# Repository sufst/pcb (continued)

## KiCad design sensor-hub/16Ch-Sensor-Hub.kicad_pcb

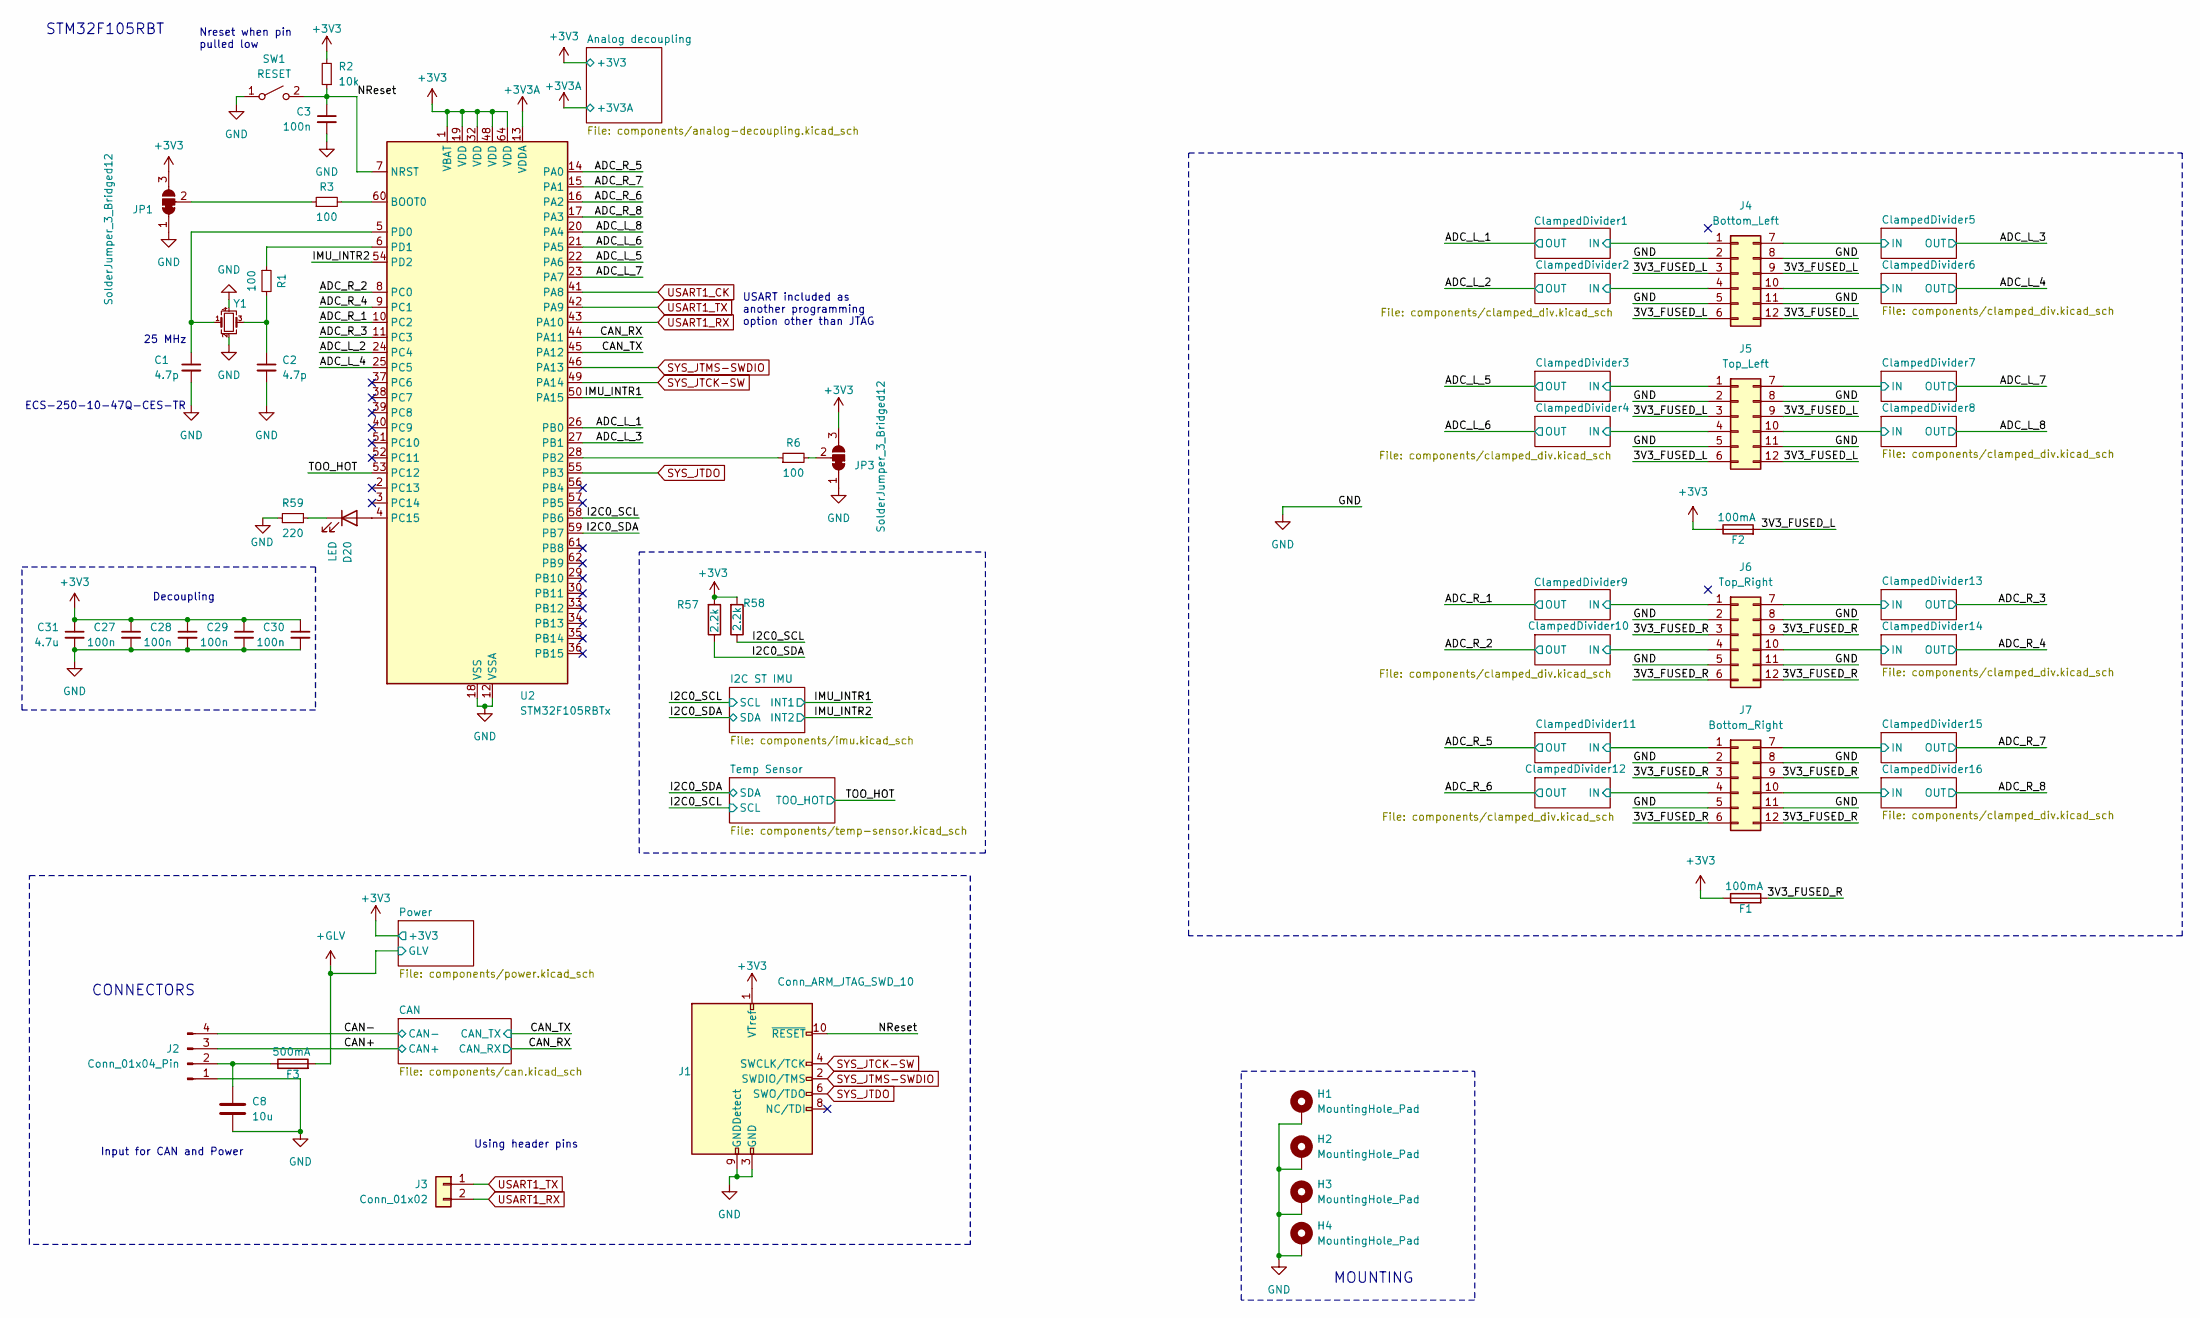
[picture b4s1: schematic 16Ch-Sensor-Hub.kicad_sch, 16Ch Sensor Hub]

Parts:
C1, C2: 4.7p; C_0603_1608Metric_Pad1.08x0.95mm_HandSolder
C3, C27, C28, C29, C30: 100n; C_0603_1608Metric_Pad1.08x0.95mm_HandSolder
C8: 10u; C_0603_1608Metric_Pad1.08x0.95mm_HandSolder
C31: 4.7u; C_0603_1608Metric_Pad1.08x0.95mm_HandSolder
D20: LED; LED_0603_1608Metric_Pad1.05x0.95mm_HandSolder
F1, F2: 100mA; Fuse_0603_1608Metric_Pad1.05x0.95mm_HandSolder
F3: 500mA; Fuse_0603_1608Metric_Pad1.05x0.95mm_HandSolder
H1, H2, H3, H4: MountingHole_Pad; MountingHole_3.2mm_M3_Pad_Via
J1: Conn_ARM_JTAG_SWD_10; SHF10501LDSMLC; MPN SHF-105-01-L-D-SM-LC
J2: Conn_01x04_Pin; Molex_Micro-Fit_3.0_43045-0412_2x02_P3.00mm_Vertical
J3: Conn_01x02; PinHeader_1x02_P2.54mm_Vertical
J4: Bottom_Left; Molex_Micro-Fit_3.0_43045-1200_2x06_P3.00mm_Horizontal
J5: Top_Left; Molex_Micro-Fit_3.0_43045-1200_2x06_P3.00mm_Horizontal
J6: Top_Right; Molex_Micro-Fit_3.0_43045-1200_2x06_P3.00mm_Horizontal
J7: Bottom_Right; Molex_Micro-Fit_3.0_43045-1200_2x06_P3.00mm_Horizontal
JP1, JP3: SolderJumper_3_Bridged12; SolderJumper-3_P1.3mm_Bridged12_RoundedPad1.0x1.5mm
R1, R3, R6: 100; R_0603_1608Metric_Pad0.98x0.95mm_HandSolder
R2: 10k; R_0603_1608Metric_Pad0.98x0.95mm_HandSolder
R57, R58: 2.2k; R_0603_1608Metric_Pad0.98x0.95mm_HandSolder; Mouser Order Number 603-RC0402FR-072K2L
R59: 220; R_0603_1608Metric_Pad0.98x0.95mm_HandSolder
SW1: RESET; SW_Push_1P1T_NO_CK_KMR2; MPN KMR221NG LFS
U2: STM32F105RBTx; LQFP-64_10x10mm_P0.5mm
Y1: ECS-250-10-47Q-CES-TR; Resonator_SMD_ECS_ECX-1247Q_1.6x1.2x0.3mm; MPN ECS-250-10-47Q-CES-TR

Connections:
+3V3: C27.1, C28.1, C29.1, C30.1, C31.1, F1.1, F2.1, J1.1 (VTref), JP1.3 (B), JP3.3 (B), R2.2, R57.2, R58.2, U2.1 (VBAT), U2.19 (VDD), U2.32 (VDD), U2.48 (VDD), U2.64 (VDD); also elsewhere on the board
+3V3A: U2.13 (VDDA); also elsewhere on the board
+GLV: F3.2; also elsewhere on the board
/3V3_FUSED_L: F2.2, J4.3, J4.6, J4.9, J4.12, J5.3, J5.6, J5.9, J5.12
/3V3_FUSED_R: F1.2, J6.3, J6.6, J6.9, J6.12, J7.3, J7.6, J7.9, J7.12
/ADC_L_1: U2.26 (PB0); also elsewhere on the board
/ADC_L_2: U2.24 (PC4); also elsewhere on the board
/ADC_L_3: U2.27 (PB1); also elsewhere on the board
/ADC_L_4: U2.25 (PC5); also elsewhere on the board
/ADC_L_5: U2.22 (PA6); also elsewhere on the board
/ADC_L_6: U2.21 (PA5); also elsewhere on the board
/ADC_L_7: U2.23 (PA7); also elsewhere on the board
/ADC_L_8: U2.20 (PA4); also elsewhere on the board
/ADC_R_1: U2.10 (PC2); also elsewhere on the board
/ADC_R_2: U2.8 (PC0); also elsewhere on the board
/ADC_R_3: U2.11 (PC3); also elsewhere on the board
/ADC_R_4: U2.9 (PC1); also elsewhere on the board
/ADC_R_5: U2.14 (PA0); also elsewhere on the board
/ADC_R_6: U2.16 (PA2); also elsewhere on the board
/ADC_R_7: U2.15 (PA1); also elsewhere on the board
/ADC_R_8: U2.17 (PA3); also elsewhere on the board
/CAN+: J2.3; also elsewhere on the board
/CAN-: J2.4; also elsewhere on the board
/CAN_RX: U2.44 (PA11); also elsewhere on the board
/CAN_TX: U2.45 (PA12); also elsewhere on the board
/ClampedDivider1/IN: J4.1; also elsewhere on the board
/ClampedDivider2/IN: J4.4; also elsewhere on the board
/ClampedDivider3/IN: J5.1; also elsewhere on the board
/ClampedDivider4/IN: J5.4; also elsewhere on the board
/ClampedDivider5/IN: J4.7; also elsewhere on the board
/ClampedDivider6/IN: J4.10; also elsewhere on the board
/ClampedDivider7/IN: J5.7; also elsewhere on the board
/ClampedDivider8/IN: J5.10; also elsewhere on the board
/ClampedDivider9/IN: J6.1; also elsewhere on the board
/ClampedDivider10/IN: J6.4; also elsewhere on the board
/ClampedDivider11/IN: J7.1; also elsewhere on the board
/ClampedDivider12/IN: J7.4; also elsewhere on the board
/ClampedDivider13/IN: J6.7; also elsewhere on the board
/ClampedDivider14/IN: J6.10; also elsewhere on the board
/ClampedDivider15/IN: J7.7; also elsewhere on the board
/ClampedDivider16/IN: J7.10; also elsewhere on the board
/I2C0_SCL: R58.1, U2.58 (PB6); also elsewhere on the board
/I2C0_SDA: R57.1, U2.59 (PB7); also elsewhere on the board
/IMU_INTR1: U2.50 (PA15); also elsewhere on the board
/IMU_INTR2: U2.54 (PD2); also elsewhere on the board
/NReset: C3.1, J1.10 (~RESET), R2.1, SW1.2 (B), U2.7 (NRST)
/TOO_HOT: U2.53 (PC12); also elsewhere on the board
GND: C1.2, C2.2, C3.2, C8.2, C27.2, C28.2, C29.2, C30.2, C31.2, H1.1, H2.1, H3.1, H4.1, J1.3 (GND), J1.5 (GND), J1.9 (GNDDetect), J2.1, J4.2, J4.5, J4.8, J4.11, J5.2, J5.5, J5.8, J5.11, J6.2, J6.5, J6.8, J6.11, J7.2, J7.5, J7.8, J7.11, JP1.1 (A), JP3.1 (A), R59.1, SW1.1 (A), U2.12 (VSSA), U2.18 (VSS), U2.31 (VSS), U2.47 (VSS), U2.63 (VSS), Y1.2, Y1.4; also elsewhere on the board
unnamed: C2.1, R1.2, Y1.3
unnamed: D20.2 (A), U2.4 (PC15)
unnamed: D20.1 (K), R59.2
unnamed: C8.1, F3.1, J2.2
unnamed: JP1.2 (C), R3.1
unnamed: JP3.2 (C), R6.2
unnamed: R3.2, U2.60 (BOOT0)
unnamed: R6.1, U2.28 (PB2)
unnamed: C1.1, U2.5 (PD0), Y1.1
unnamed: R1.1, U2.6 (PD1)
SYS_JTCK-SW: J1.4 (SWCLK/TCK), U2.49 (PA14)
SYS_JTDO: J1.6 (SWO/TDO), U2.55 (PB3)
SYS_JTMS-SWDIO: J1.2 (SWDIO/TMS), U2.46 (PA13)
USART1_CK: U2.41 (PA8)
USART1_RX: J3.2, U2.43 (PA10)
USART1_TX: J3.1, U2.42 (PA9)

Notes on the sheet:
25 MHz
STM32F105RBT
Input for CAN and Power
CONNECTORS
Nreset when pin pulled low
ECS-250-10-47Q-CES-TR
Decoupling
Using header pins
USART included as another programming option other than JTAG
MOUNTING

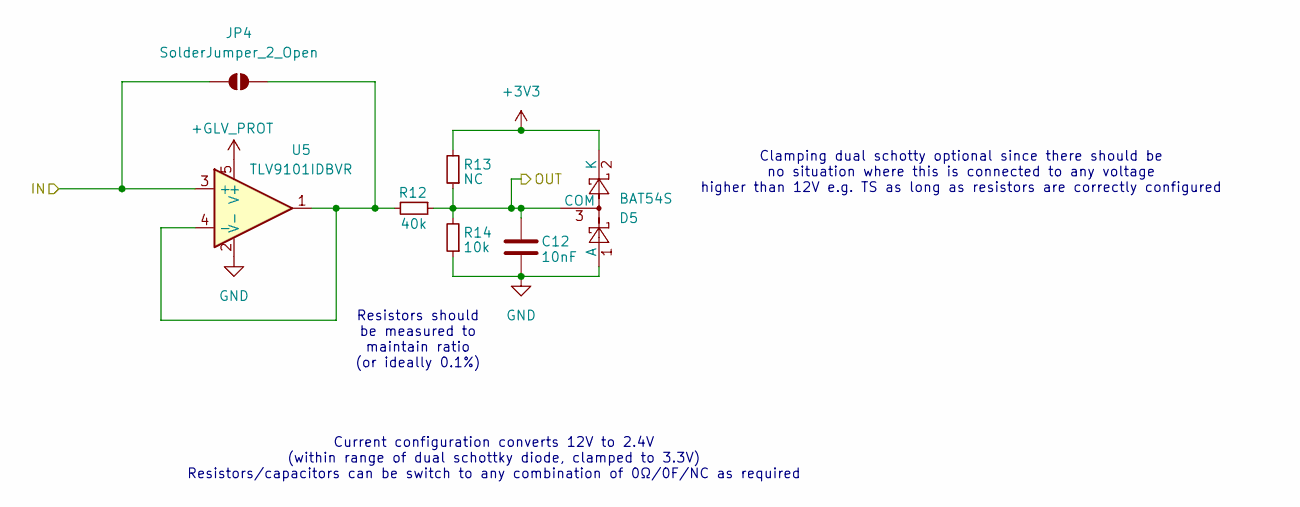
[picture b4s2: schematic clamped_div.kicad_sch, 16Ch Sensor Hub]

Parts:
C12: 10nF; C_0603_1608Metric_Pad1.08x0.95mm_HandSolder
D5: BAT54S; SOT-23
JP4: SolderJumper_2_Open; SolderJumper-2_P1.3mm_Open_RoundedPad1.0x1.5mm
R12: 40k; R_0603_1608Metric_Pad0.98x0.95mm_HandSolder; Manufacturer_Part_Number CRCW080540K0FKEA; Mouser Part Number 71-CRCW080540K0FKEA
R13: NC; R_0603_1608Metric_Pad0.98x0.95mm_HandSolder; Manufacturer_Part_Number CRGH0805F12R; Mouser Part Number 279-CRGH0805F12R
R14: 10k; R_0603_1608Metric_Pad0.98x0.95mm_HandSolder; Manufacturer_Part_Number CRGH0805F12R; Mouser Part Number 279-CRGH0805F12R
U5: TLV9101IDBVR; SOT-23-5_HandSoldering

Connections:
+3V3: D5.2 (K), R13.2; also elsewhere on the board
+GLV_PROT: U5.5 (V+); also elsewhere on the board
/ADC_L_4: C12.1, D5.3 (COM), R12.1, R13.1, R14.2; also elsewhere on the board
/ClampedDivider6/IN: JP4.1 (A), U5.3 (+); also elsewhere on the board
GND: C12.2, D5.1 (A), R14.1, U5.2 (V-); also elsewhere on the board
unnamed: JP4.2 (B), R12.2, U5.1, U5.4 (-)

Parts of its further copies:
C11, C13, C14, C15, C16, C17, C18, C19, C20, C21, C22, C23, C24, C25, C26: 10nF; C_0603_1608Metric_Pad1.08x0.95mm_HandSolder
D4, D6, D7, D8, D9, D10, D11, D12, D13, D14, D15, D16, D17, D18, D19: BAT54S; SOT-23
JP5, JP6, JP7, JP8, JP9, JP10, JP11, JP12, JP13, JP14, JP15, JP16, JP17, JP18, JP19: SolderJumper_2_Open; SolderJumper-2_P1.3mm_Open_RoundedPad1.0x1.5mm
R9, R15, R18, R21, R24, R27, R30, R33, R36, R39, R42, R45, R48, R51, R54: 40k; R_0603_1608Metric_Pad0.98x0.95mm_HandSolder; Manufacturer_Part_Number CRCW080540K0FKEA; Mouser Part Number 71-CRCW080540K0FKEA
R10, R16, R19, R22, R25, R28, R31, R34, R37, R40, R43, R46, R49, R52, R55: NC; R_0603_1608Metric_Pad0.98x0.95mm_HandSolder; Manufacturer_Part_Number CRGH0805F12R; Mouser Part Number 279-CRGH0805F12R
R11, R17, R20, R23, R26, R29, R32, R35, R38, R41, R44, R47, R50, R53, R56: 10k; R_0603_1608Metric_Pad0.98x0.95mm_HandSolder; Manufacturer_Part_Number CRGH0805F12R; Mouser Part Number 279-CRGH0805F12R
U4, U6, U7, U8, U9, U10, U11, U12, U13, U14, U15, U16, U17, U18, U19: TLV9101IDBVR; SOT-23-5_HandSoldering

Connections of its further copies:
+3V3: D4.2 (K), D6.2 (K), D7.2 (K), D8.2 (K), D9.2 (K), D10.2 (K), D11.2 (K), D12.2 (K), D13.2 (K), D14.2 (K), D15.2 (K), D16.2 (K), D17.2 (K), D18.2 (K), D19.2 (K), R10.2, R16.2, R19.2, R22.2, R25.2, R28.2, R31.2, R34.2, R37.2, R40.2, R43.2, R46.2, R49.2, R52.2, R55.2; also elsewhere on the board
+GLV_PROT: U4.5 (V+), U6.5 (V+), U7.5 (V+), U8.5 (V+), U9.5 (V+), U10.5 (V+), U11.5 (V+), U12.5 (V+), U13.5 (V+), U14.5 (V+), U15.5 (V+), U16.5 (V+), U17.5 (V+), U18.5 (V+), U19.5 (V+); also elsewhere on the board
/ADC_L_1: C15.1, D8.3 (COM), R21.1, R22.1, R23.2; also elsewhere on the board
/ADC_L_2: C16.1, D9.3 (COM), R24.1, R25.1, R26.2; also elsewhere on the board
/ADC_L_3: C11.1, D4.3 (COM), R9.1, R10.1, R11.2; also elsewhere on the board
/ADC_L_5: C17.1, D10.3 (COM), R27.1, R28.1, R29.2; also elsewhere on the board
/ADC_L_6: C18.1, D11.3 (COM), R30.1, R31.1, R32.2; also elsewhere on the board
/ADC_L_7: C13.1, D6.3 (COM), R15.1, R16.1, R17.2; also elsewhere on the board
/ADC_L_8: C14.1, D7.3 (COM), R18.1, R19.1, R20.2; also elsewhere on the board
/ADC_R_1: C23.1, D16.3 (COM), R45.1, R46.1, R47.2; also elsewhere on the board
/ADC_R_2: C24.1, D17.3 (COM), R48.1, R49.1, R50.2; also elsewhere on the board
/ADC_R_3: C19.1, D12.3 (COM), R33.1, R34.1, R35.2; also elsewhere on the board
/ADC_R_4: C20.1, D13.3 (COM), R36.1, R37.1, R38.2; also elsewhere on the board
/ADC_R_5: C25.1, D18.3 (COM), R51.1, R52.1, R53.2; also elsewhere on the board
/ADC_R_6: C26.1, D19.3 (COM), R54.1, R55.1, R56.2; also elsewhere on the board
/ADC_R_7: C21.1, D14.3 (COM), R39.1, R40.1, R41.2; also elsewhere on the board
/ADC_R_8: C22.1, D15.3 (COM), R42.1, R43.1, R44.2; also elsewhere on the board
/ClampedDivider1/IN: JP8.1 (A), U8.3 (+); also elsewhere on the board
/ClampedDivider2/IN: JP9.1 (A), U9.3 (+); also elsewhere on the board
/ClampedDivider3/IN: JP10.1 (A), U10.3 (+); also elsewhere on the board
/ClampedDivider4/IN: JP11.1 (A), U11.3 (+); also elsewhere on the board
/ClampedDivider5/IN: JP5.1 (A), U4.3 (+); also elsewhere on the board
/ClampedDivider7/IN: JP6.1 (A), U6.3 (+); also elsewhere on the board
/ClampedDivider8/IN: JP7.1 (A), U7.3 (+); also elsewhere on the board
/ClampedDivider9/IN: JP16.1 (A), U16.3 (+); also elsewhere on the board
/ClampedDivider10/IN: JP17.1 (A), U17.3 (+); also elsewhere on the board
/ClampedDivider11/IN: JP18.1 (A), U18.3 (+); also elsewhere on the board
/ClampedDivider12/IN: JP19.1 (A), U19.3 (+); also elsewhere on the board
/ClampedDivider13/IN: JP12.1 (A), U12.3 (+); also elsewhere on the board
/ClampedDivider14/IN: JP13.1 (A), U13.3 (+); also elsewhere on the board
/ClampedDivider15/IN: JP14.1 (A), U14.3 (+); also elsewhere on the board
/ClampedDivider16/IN: JP15.1 (A), U15.3 (+); also elsewhere on the board
GND: C11.2, C13.2, C14.2, C15.2, C16.2, C17.2, C18.2, C19.2, C20.2, C21.2, C22.2, C23.2, C24.2, C25.2, C26.2, D4.1 (A), D6.1 (A), D7.1 (A), D8.1 (A), D9.1 (A), D10.1 (A), D11.1 (A), D12.1 (A), D13.1 (A), D14.1 (A), D15.1 (A), D16.1 (A), D17.1 (A), D18.1 (A), D19.1 (A), R11.1, R17.1, R20.1, R23.1, R26.1, R29.1, R32.1, R35.1, R38.1, R41.1, R44.1, R47.1, R50.1, R53.1, R56.1, U4.2 (V-), U6.2 (V-), U7.2 (V-), U8.2 (V-), U9.2 (V-), U10.2 (V-), U11.2 (V-), U12.2 (V-), U13.2 (V-), U14.2 (V-), U15.2 (V-), U16.2 (V-), U17.2 (V-), U18.2 (V-), U19.2 (V-); also elsewhere on the board
unnamed: JP5.2 (B), R9.2, U4.1, U4.4 (-)
unnamed: JP6.2 (B), R15.2, U6.1, U6.4 (-)
unnamed: JP7.2 (B), R18.2, U7.1, U7.4 (-)
unnamed: JP8.2 (B), R21.2, U8.1, U8.4 (-)
unnamed: JP9.2 (B), R24.2, U9.1, U9.4 (-)
unnamed: JP10.2 (B), R27.2, U10.1, U10.4 (-)
unnamed: JP11.2 (B), R30.2, U11.1, U11.4 (-)
unnamed: JP12.2 (B), R33.2, U12.1, U12.4 (-)
unnamed: JP13.2 (B), R36.2, U13.1, U13.4 (-)
unnamed: JP14.2 (B), R39.2, U14.1, U14.4 (-)
unnamed: JP15.2 (B), R42.2, U15.1, U15.4 (-)
unnamed: JP16.2 (B), R45.2, U16.1, U16.4 (-)
unnamed: JP17.2 (B), R48.2, U17.1, U17.4 (-)
unnamed: JP18.2 (B), R51.2, U18.1, U18.4 (-)
unnamed: JP19.2 (B), R54.2, U19.1, U19.4 (-)

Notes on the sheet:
Current configuration converts 12V to 2.4V (within range of dual schottky diode, clamped to 3.3V) Resistors/capacitors can be switch to any combination of 0Ω/0F/NC as required
Clamping dual schotty optional since there should be no situation where this is connected to any voltage higher than 12V e.g. TS as long as resistors are correctly configured
Resistors should be measured to maintain ratio (or ideally 0.1%)

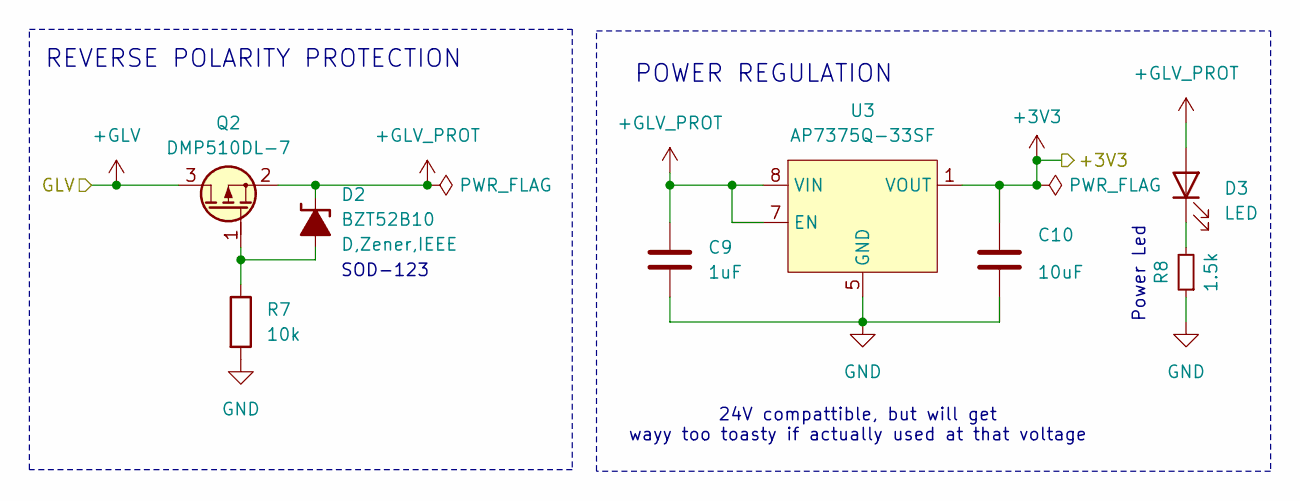
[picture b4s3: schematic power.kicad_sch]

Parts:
C9: 1uF; C_0603_1608Metric_Pad1.08x0.95mm_HandSolder
C10: 10uF; C_0603_1608Metric_Pad1.08x0.95mm_HandSolder
D2: BZT52B10; D_SOD-123; MPN BZT52B10
D3: LED; LED_0603_1608Metric_Pad1.05x0.95mm_HandSolder
Q2: DMP510DL-7; SOT-23
R7: 10k; R_0603_1608Metric_Pad0.98x0.95mm_HandSolder
R8: 1.5k; R_0603_1608Metric_Pad0.98x0.95mm_HandSolder
U3: AP7375Q-33SF; Diodes_SO-8EP

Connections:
+3V3: C10.1, U3.1 (VOUT); also elsewhere on the board
+GLV: Q2.3 (D); also elsewhere on the board
+GLV_PROT: C9.1, D2.1 (K-), D3.2 (A), Q2.2 (S), U3.7 (EN), U3.8 (VIN); also elsewhere on the board
GND: C9.2, C10.2, R7.2, R8.1, U3.2, U3.3, U3.4, U3.5 (GND), U3.6, U3.9 (EP); also elsewhere on the board
unnamed: D2.2 (A+), Q2.1 (G), R7.1
unnamed: D3.1 (K), R8.2

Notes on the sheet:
24V compattible, but will get wayy too toasty if actually used at that voltage
Power Led
POWER REGULATION
SOD-123
REVERSE POLARITY PROTECTION

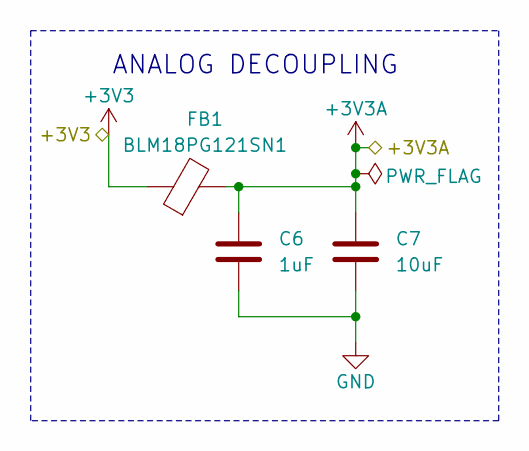
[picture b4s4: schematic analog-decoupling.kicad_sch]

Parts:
C6: 1uF; C_0603_1608Metric_Pad1.08x0.95mm_HandSolder
C7: 10uF; C_0603_1608Metric_Pad1.08x0.95mm_HandSolder
FB1: BLM18PG121SN1; L_0603_1608Metric_Pad1.05x0.95mm_HandSolder

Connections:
+3V3: FB1.1; also elsewhere on the board
+3V3A: C6.1, C7.1, FB1.2; also elsewhere on the board
GND: C6.2, C7.2; also elsewhere on the board

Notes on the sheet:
ANALOG DECOUPLING

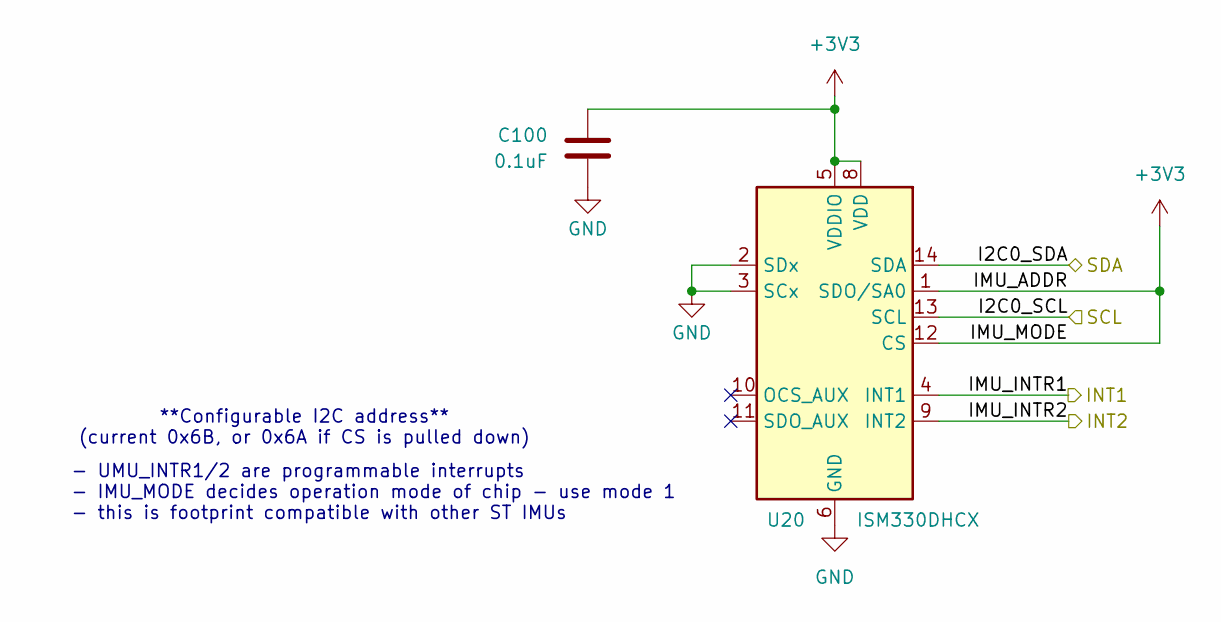
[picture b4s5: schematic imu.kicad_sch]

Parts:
C100: 0.1uF; C_0603_1608Metric_Pad1.08x0.95mm_HandSolder; Mouser Order Number 81-GRM155R62A104KE4J
U20: ISM330DHCX; LGA-14_3x2.5mm_P0.5mm_LayoutBorder3x4y; Mouser Order Number 511-ISM330DHCXTR

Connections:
+3V3: C100.2, U20.1 (SDO/SA0), U20.5 (VDDIO), U20.8 (VDD), U20.12 (CS); also elsewhere on the board
/I2C0_SCL: U20.13 (SCL); also elsewhere on the board
/I2C0_SDA: U20.14 (SDA); also elsewhere on the board
/IMU_INTR1: U20.4 (INT1); also elsewhere on the board
/IMU_INTR2: U20.9 (INT2); also elsewhere on the board
GND: C100.1, U20.2 (SDx), U20.3 (SCx), U20.6 (GND), U20.7 (GND); also elsewhere on the board

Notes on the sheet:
- UMU_INTR1/2 are programmable interrupts - IMU_MODE decides operation mode of chip - use mode 1 - this is footprint compatible with other ST IMUs
**Configurable I2C address** (current 0x6B, or 0x6A if CS is pulled down)

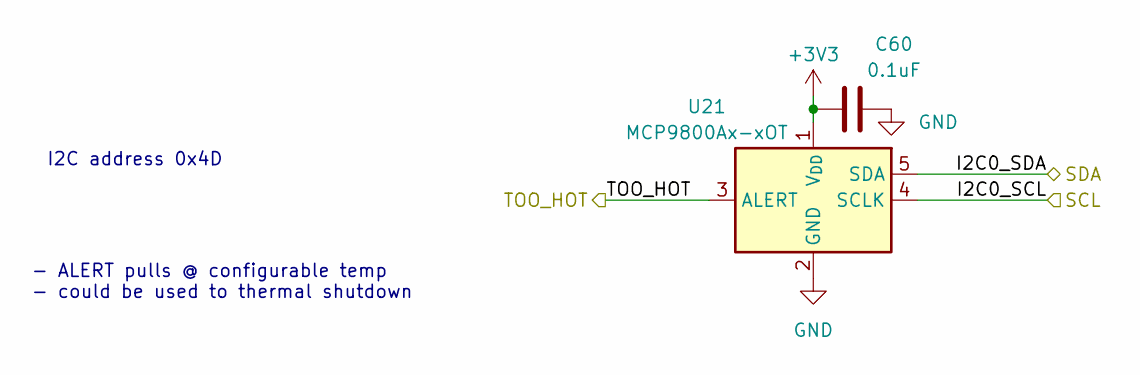
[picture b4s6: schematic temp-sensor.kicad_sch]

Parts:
C60: 0.1uF; C_0603_1608Metric_Pad1.08x0.95mm_HandSolder; Mouser Order Number 81-GRM155R62A104KE4J
U21: MCP9800Ax-xOT; SOT-23-5; Mouser Order Number 579-MCP9800A5T-M/OT

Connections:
+3V3: C60.1, U21.1 (V_{DD}); also elsewhere on the board
/I2C0_SCL: U21.4 (SCLK); also elsewhere on the board
/I2C0_SDA: U21.5 (SDA); also elsewhere on the board
/TOO_HOT: U21.3 (ALERT); also elsewhere on the board
GND: C60.2, U21.2 (GND); also elsewhere on the board

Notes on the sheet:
- ALERT pulls @ configurable temp - could be used to thermal shutdown
I2C address 0x4D

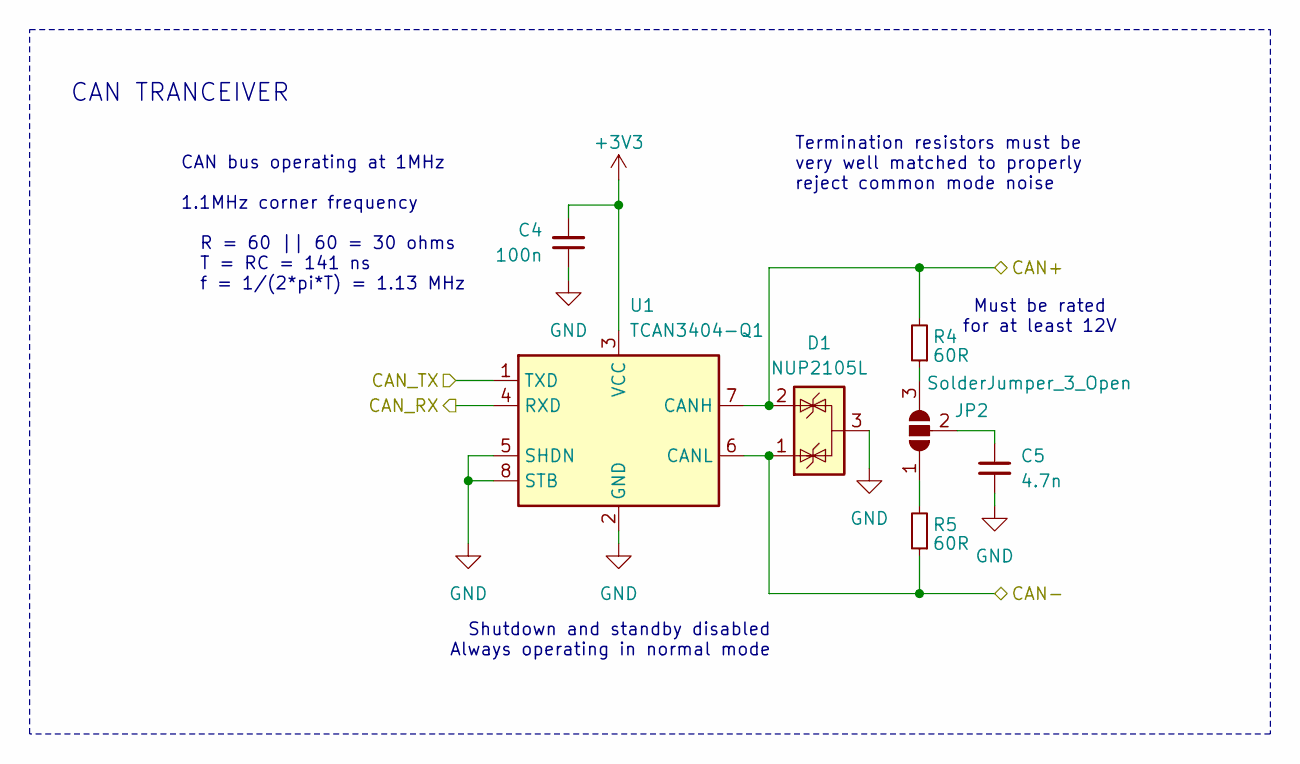
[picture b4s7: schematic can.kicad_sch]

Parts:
C4: 100n; C_0603_1608Metric_Pad1.08x0.95mm_HandSolder
C5: 4.7n; C_0603_1608Metric_Pad1.08x0.95mm_HandSolder
D1: NUP2105L; SOT-23; MPN NUP2105L
JP2: SolderJumper_3_Open; SolderJumper-3_P1.3mm_Open_RoundedPad1.0x1.5mm
R4, R5: 60R; R_0603_1608Metric_Pad0.98x0.95mm_HandSolder
U1: TCAN3404-Q1; SOT-23-8_Handsoldering; MPN TCAN3404DDFRQ1

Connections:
+3V3: C4.2, U1.3 (VCC); also elsewhere on the board
/CAN+: D1.2 (K), R4.2, U1.7 (CANH); also elsewhere on the board
/CAN-: D1.1 (K), R5.1, U1.6 (CANL); also elsewhere on the board
/CAN_RX: U1.4 (RXD); also elsewhere on the board
/CAN_TX: U1.1 (TXD); also elsewhere on the board
GND: C4.1, C5.2, D1.3 (A), U1.2 (GND), U1.5 (SHDN), U1.8 (STB); also elsewhere on the board
unnamed: JP2.1 (A), R5.2
unnamed: JP2.3 (B), R4.1
unnamed: C5.1, JP2.2 (C)

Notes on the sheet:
CAN TRANCEIVER
Termination resistors must be very well matched to properly reject common mode noise
CAN bus operating at 1MHz 1.1MHz corner frequency R = 60 || 60 = 30 ohms T = RC = 141 ns f = 1/(2*pi*T) = 1.13 MHz
Must be rated for at least 12V
Shutdown and standby disabled Always operating in normal mode

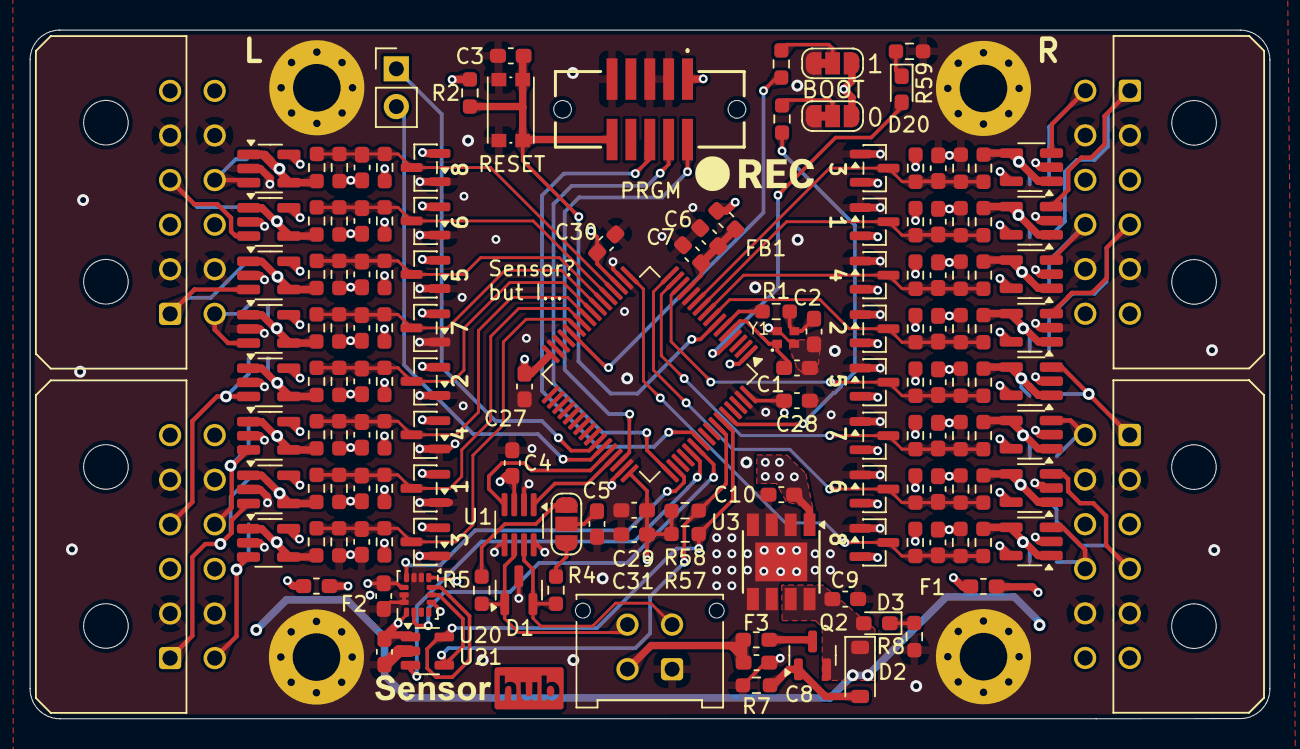
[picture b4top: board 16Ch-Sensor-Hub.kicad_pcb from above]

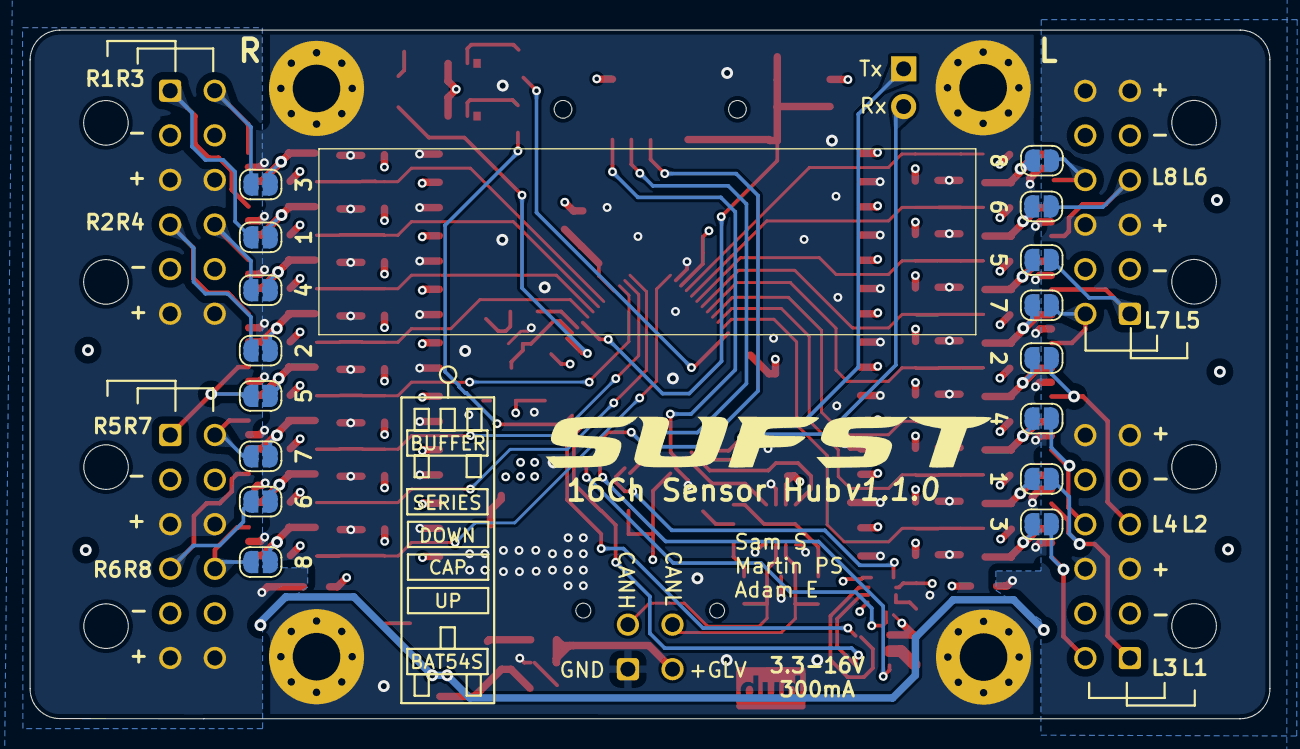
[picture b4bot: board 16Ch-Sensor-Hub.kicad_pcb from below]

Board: 4 copper layers, 83.4 x 46.3 mm, 170 parts (16 on the bottom side), 85 nets.

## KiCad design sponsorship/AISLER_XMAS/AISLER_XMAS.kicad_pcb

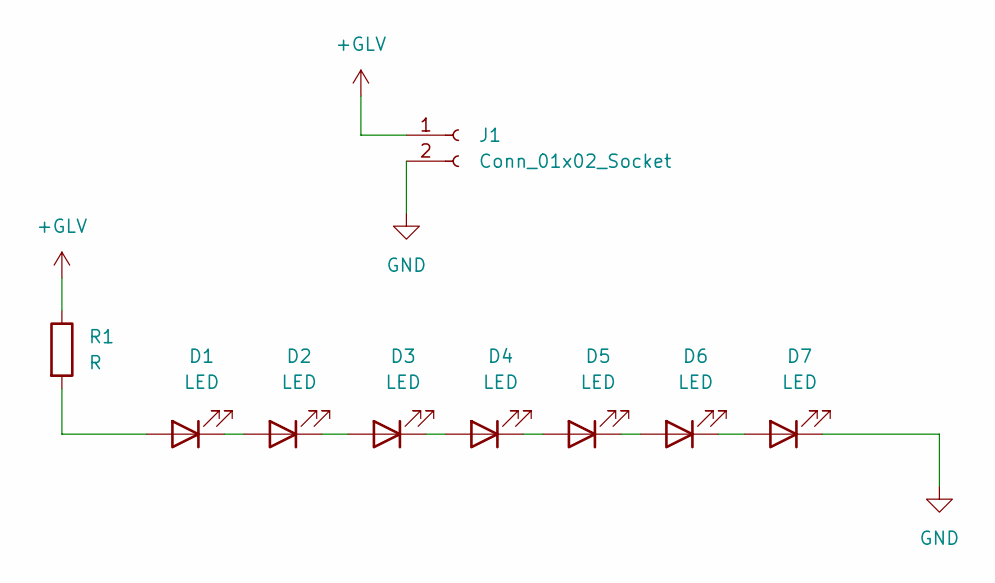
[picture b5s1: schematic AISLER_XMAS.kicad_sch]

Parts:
D1, D2, D3, D4, D5, D6, D7: LED; LED_D5.0mm_Clear
J1: Conn_01x02_Socket; AMASS_XT30PW-M_1x02_P2.50mm_Horizontal
R1: R; R_Axial_DIN0207_L6.3mm_D2.5mm_P7.62mm_Horizontal

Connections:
+GLV: J1.1, R1.1
GND: D7.1 (K), J1.2
unnamed: D1.2 (A), R1.2
unnamed: D1.1 (K), D2.2 (A)
unnamed: D2.1 (K), D3.2 (A)
unnamed: D3.1 (K), D4.2 (A)
unnamed: D4.1 (K), D5.2 (A)
unnamed: D5.1 (K), D6.2 (A)
unnamed: D6.1 (K), D7.2 (A)

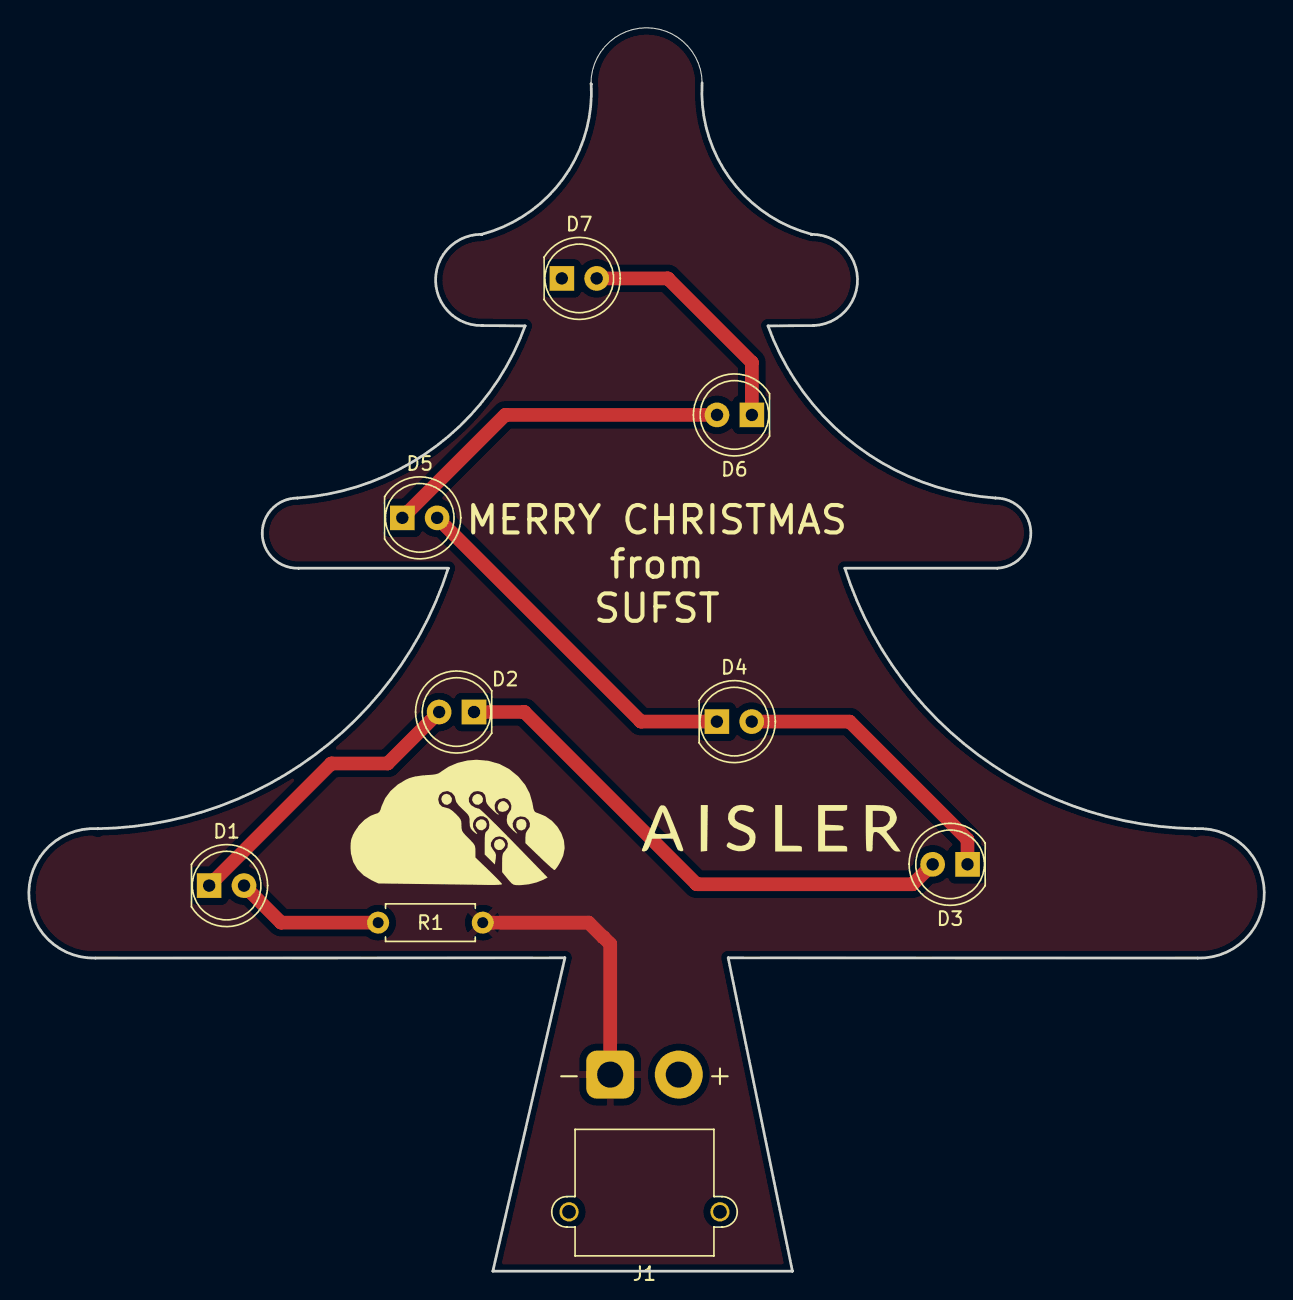
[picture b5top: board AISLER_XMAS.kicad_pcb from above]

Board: 2 copper layers, 90.0 x 90.6 mm, 9 parts (0 on the bottom side), 9 nets.

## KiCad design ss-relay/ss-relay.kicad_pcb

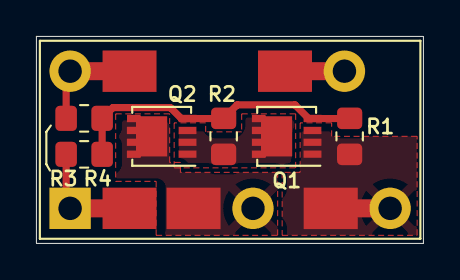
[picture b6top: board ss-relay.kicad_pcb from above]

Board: 2 copper layers, 21.5 x 11.5 mm, 7 parts (0 on the bottom side), 6 nets.

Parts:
K1: G5Q-1EU DC12; Relay_Template
Q1, Q2: SiS413DNT; Vishay_PowerPAK_1212-8_Single
R1, R2: 10k; R_0805_2012Metric_Pad1.20x1.40mm_HandSolder
R3, R4: 0; R_0805_2012Metric_Pad1.20x1.40mm_HandSolder

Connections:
/COIL1: K1.1, R4.2
/COIL2: K1.5, R3.1
/COM: K1.2, Q2.5 (D)
/N/O: K1.3, Q1.1 (S), Q1.2 (S), Q1.3 (S), R1.1
unnamed: Q1.5 (D), Q2.1 (S), Q2.2 (S), Q2.3 (S), R2.1
unnamed: Q1.4 (G), Q2.4 (G), R1.2, R2.2, R3.2, R4.1

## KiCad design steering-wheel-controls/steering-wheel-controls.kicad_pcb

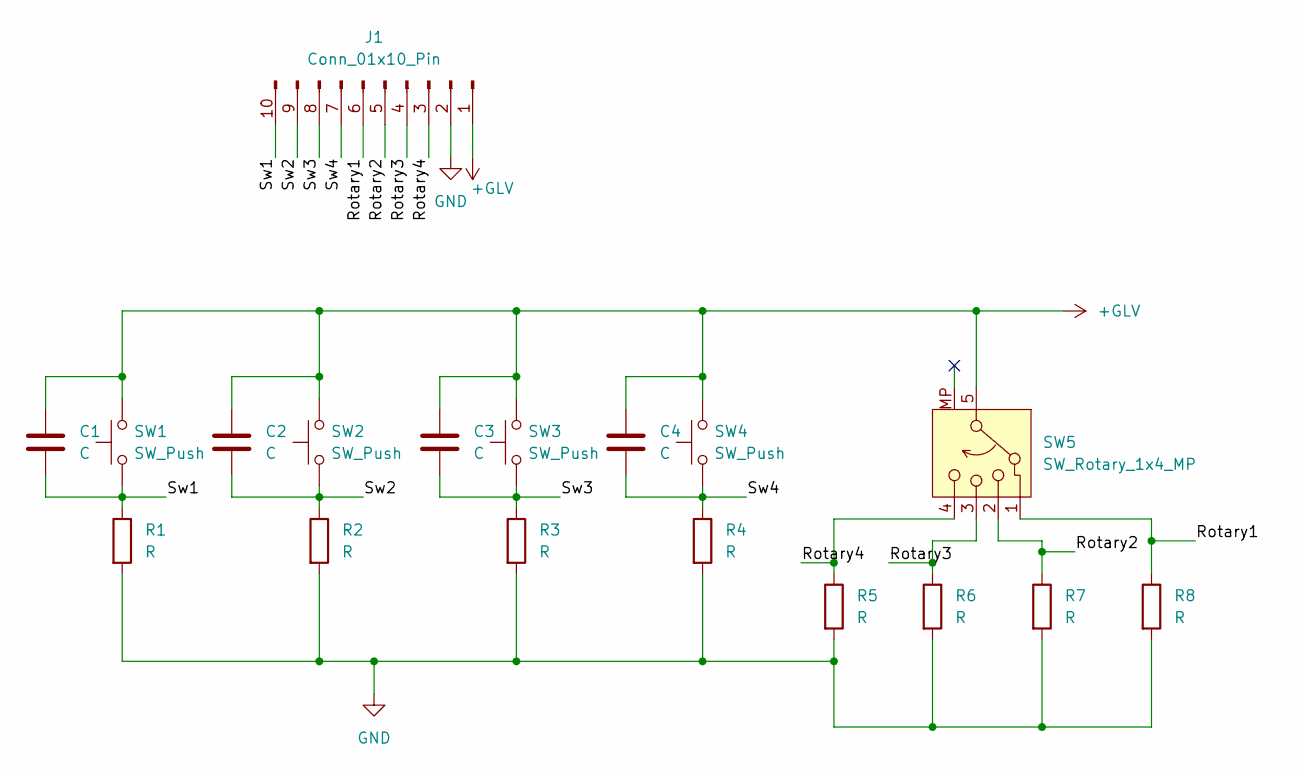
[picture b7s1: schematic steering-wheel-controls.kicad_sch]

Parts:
C1, C2, C3, C4: C; C_0805_2012Metric_Pad1.18x1.45mm_HandSolder
J1: Conn_01x10_Pin; PinSocket_1x10_P2.54mm_Vertical
R1, R2, R3, R4, R5, R6, R7, R8: R; R_0805_2012Metric_Pad1.20x1.40mm_HandSolder
SW1, SW2, SW3, SW4: SW_Push; PinSocket_1x02_P2.54mm_Vertical
SW5: SW_Rotary_1x4_MP; PinSocket_1x05_P2.54mm_Vertical

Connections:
+GLV: C1.1, C2.1, C3.1, C4.1, J1.1, SW1.2, SW2.2, SW3.2, SW4.2, SW5.5
/Rotary1: J1.6, R8.1, SW5.1
/Rotary2: J1.5, R7.1, SW5.2
/Rotary3: J1.4, R6.1, SW5.3
/Rotary4: J1.3, R5.1, SW5.4
/Sw1: C1.2, J1.10, R1.1, SW1.1
/Sw2: C2.2, J1.9, R2.1, SW2.1
/Sw3: C3.2, J1.8, R3.1, SW3.1
/Sw4: C4.2, J1.7, R4.1, SW4.1
GND: J1.2, R1.2, R2.2, R3.2, R4.2, R5.2, R6.2, R7.2, R8.2
